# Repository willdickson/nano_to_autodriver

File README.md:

# nano_to_autodriver
A simple PCB for connecting the Arduino Nano to the Sparkfun Autodriver. 

* [Schematic (PDF)](nano_to_autodriver.pdf)

* [Bill-of-materials](BOM.txt)

# Top View: 

# Bottom View:

# License: 
Creative Commons Attribution 4.0 International CC BY 4.0

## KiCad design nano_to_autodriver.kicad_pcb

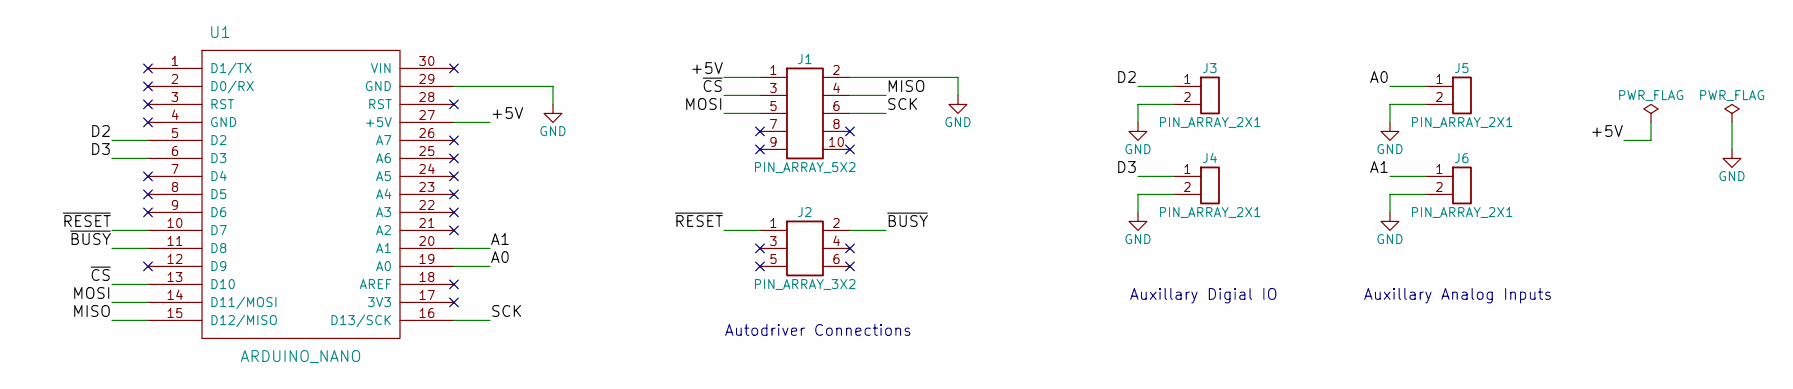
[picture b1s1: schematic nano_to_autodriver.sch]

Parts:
J1: PIN_ARRAY_5X2; 5X2_SHRD_HEADER
J2: PIN_ARRAY_3X2; 3X2_SHRD_HEADER
J3, J4, J5, J6: PIN_ARRAY_2X1; BNC
U1: ARDUINO_NANO; arduino_nano

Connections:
/+5V: J1.1, U1.27 (+5V)
/A0: J5.1, U1.19 (A0)
/A1: J6.1, U1.20 (A1)
/D2: J3.1, U1.5 (D2)
/D3: J4.1, U1.6 (D3)
/MISO: J1.4, U1.15 (D12/MISO)
/MOSI: J1.5, U1.14 (D11/MOSI)
/SCK: J1.6, U1.16 (D13/SCK)
/~BUSY: J2.2, U1.11 (D8)
/~CS: J1.3, U1.13 (D10)
/~RESET: J2.1, U1.10 (D7)
GND: J1.2, J3.2, J4.2, J5.2, J6.2, U1.29 (GND)

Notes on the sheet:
Autodriver Connections
Auxillary Digial IO
Auxillary Analog Inputs

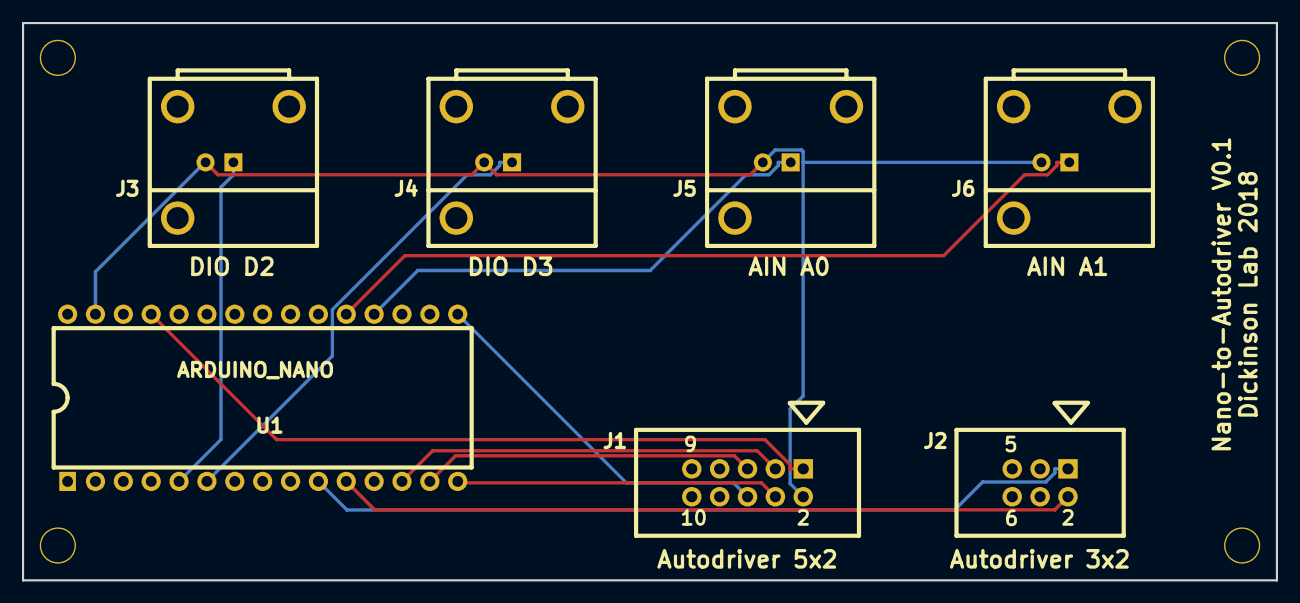
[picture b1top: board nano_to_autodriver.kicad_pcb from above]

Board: 2 copper layers, 114.3 x 50.8 mm, 11 parts (0 on the bottom side), 12 nets.

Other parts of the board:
M0, M1, M2, M3: VAL**; MOUNT_HOLE_4_40

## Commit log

2018-01-11 Project creation.
2018-01-11 Create README.md
    Added Readme with images of board.
2018-01-13 Fixed wrong image issue.
2018-01-17 Added pdf of schematic and link to it in README.
2018-01-17 Added BOM.
2018-01-17 Finished bill of materials (BOM.txt).
2018-01-17 Added link to BOM in README.
